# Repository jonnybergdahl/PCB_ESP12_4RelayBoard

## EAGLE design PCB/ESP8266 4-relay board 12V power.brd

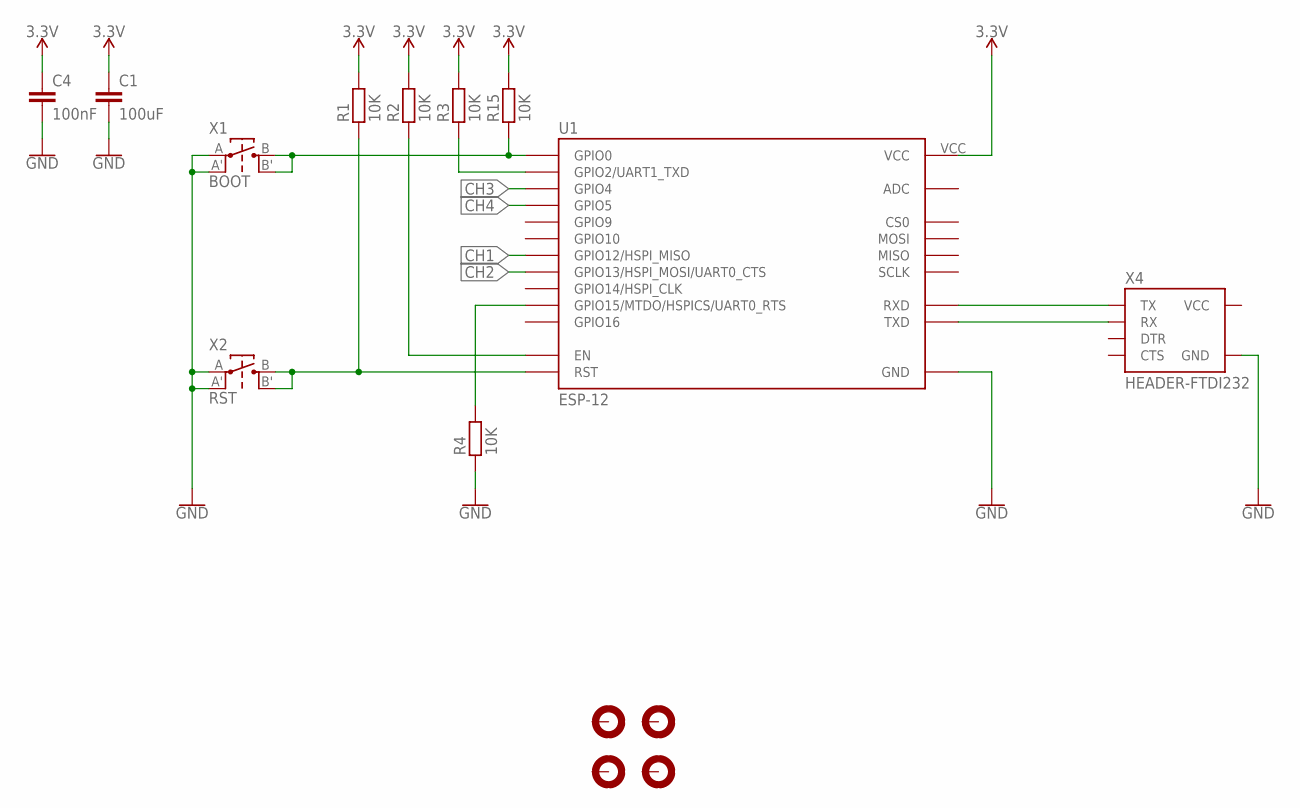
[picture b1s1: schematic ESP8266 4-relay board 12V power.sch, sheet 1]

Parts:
C1: 100uF; C0603
C4: 100nF; C0603
H1, H2, H3, H4: MOUNTHOLE-PAD3.2; 3.2-PAD
R1, R2, R3, R4, R15: 10K; R0603
U1: ESP-12; ESP-12E
X1: BOOT; TACT-SWITCH-EVQ
X2: RST; TACT-SWITCH-EVQ
X4: HEADER-FTDI232; FTDI232-1X06

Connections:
3.3V: C1.1, C4.1, R1.2, R2.2, R3.2, R15.2, U1.VCC; also elsewhere on the board
CH1: U1.GPIO12 (GPIO12/HSPI_MISO); also elsewhere on the board
CH2: U1.GPIO13 (GPIO13/HSPI_MOSI/UART0_CTS); also elsewhere on the board
CH3: U1.GPIO4; also elsewhere on the board
CH4: U1.GPIO5; also elsewhere on the board
GND: C1.2, C4.2, R4.1, U1.GND, X1.A, X1.A', X2.A, X2.A', X4.GND; also elsewhere on the board
unnamed: R4.2, U1.GPIO15 (GPIO15/MTDO/HSPICS/UART0_RTS)
unnamed: R2.1, U1.EN
unnamed: R1.1, U1.RST, X2.B, X2.B'
unnamed: R15.1, U1.GPIO0, X1.B, X1.B'
unnamed: R3.1, U1.GPIO2 (GPIO2/UART1_TXD)
RXD: U1.RXD, X4.TX
TXD: U1.TXD, X4.RX
VCC: X4.VCC

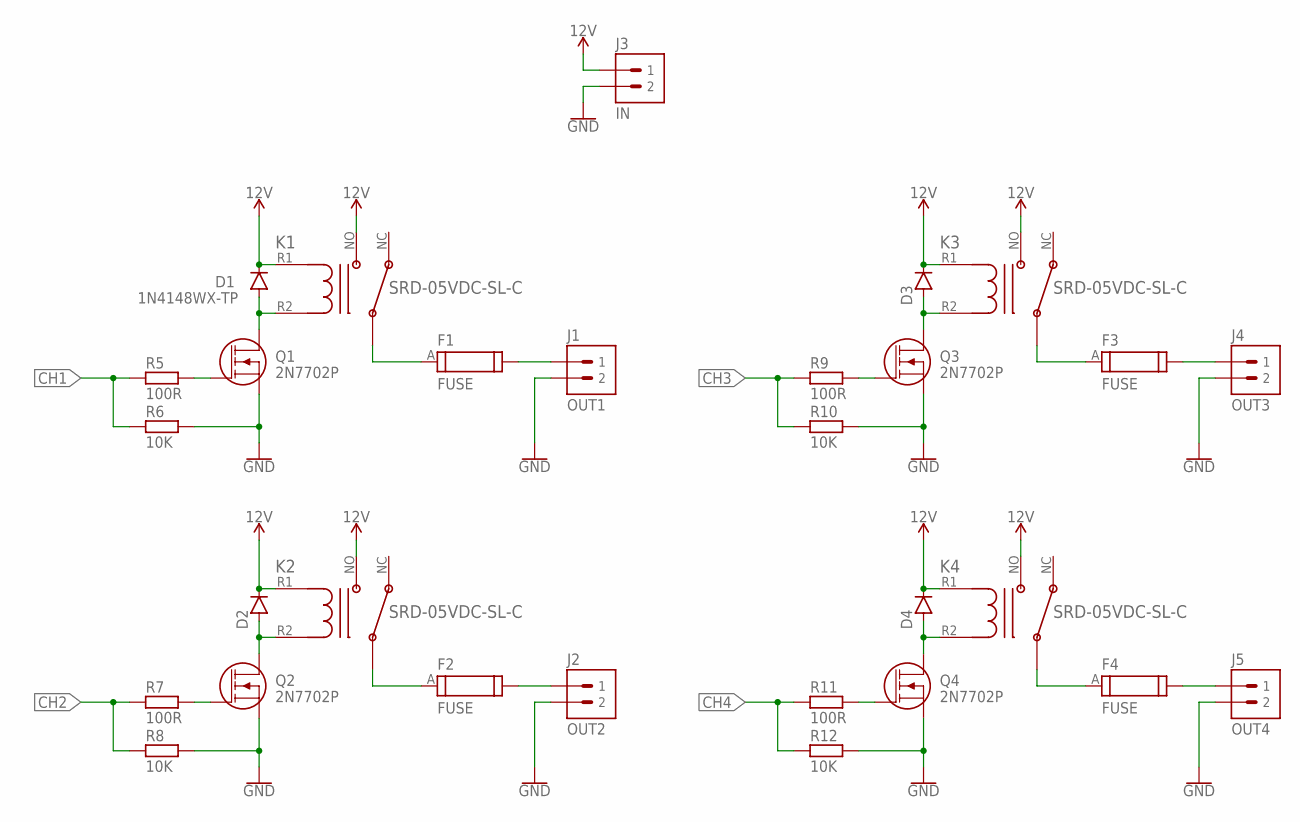
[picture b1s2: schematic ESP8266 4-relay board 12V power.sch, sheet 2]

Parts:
D1: 1N4148WX-TP; SOD-323
D2, D3, D4: DIODE1N4148WX-TP; SOD-323
F1, F2, F3, F4: FUSE; FUSE-TEAL
J1: OUT1; ONSHORE-OSTTC022162
J2: OUT2; ONSHORE-OSTTC022162
J3: IN; ONSHORE-OSTTC022162
J4: OUT3; ONSHORE-OSTTC022162
J5: OUT4; ONSHORE-OSTTC022162
K1, K2, K3, K4: SRD-05VDC-SL-C; RELAY-SRD-05VDC-SL-C
Q1, Q2, Q3, Q4: 2N7702P; SOT23-3
R5, R7, R9, R11: 100R; R0603
R6, R8, R10, R12: 10K; R0603

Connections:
12V: D1.1 (C), D2.1 (C), D3.1 (C), D4.1 (C), J3.1, K1.NO, K1.R1, K2.NO, K2.R1, K3.NO, K3.R1, K4.NO, K4.R1; also elsewhere on the board
CH1: R5.1, R6.1; also elsewhere on the board
CH2: R7.1, R8.1; also elsewhere on the board
CH3: R9.1, R10.1; also elsewhere on the board
CH4: R11.1, R12.1; also elsewhere on the board
GND: J1.2, J2.2, J3.2, J4.2, J5.2, Q1.2 (S), Q2.2 (S), Q3.2 (S), Q4.2 (S), R6.2, R8.2, R10.2, R12.2; also elsewhere on the board
unnamed: D1.2 (A), K1.R2, Q1.3 (D)
unnamed: F1.A, K1.C
unnamed: F1.B, J1.1
unnamed: Q1.1 (G), R5.2
unnamed: D2.2 (A), K2.R2, Q2.3 (D)
unnamed: Q2.1 (G), R7.2
unnamed: F2.A, K2.C
unnamed: F2.B, J2.1
unnamed: D3.2 (A), K3.R2, Q3.3 (D)
unnamed: F3.A, K3.C
unnamed: F3.B, J4.1
unnamed: Q3.1 (G), R9.2
unnamed: D4.2 (A), K4.R2, Q4.3 (D)
unnamed: Q4.1 (G), R11.2
unnamed: F4.A, K4.C
unnamed: F4.B, J5.1

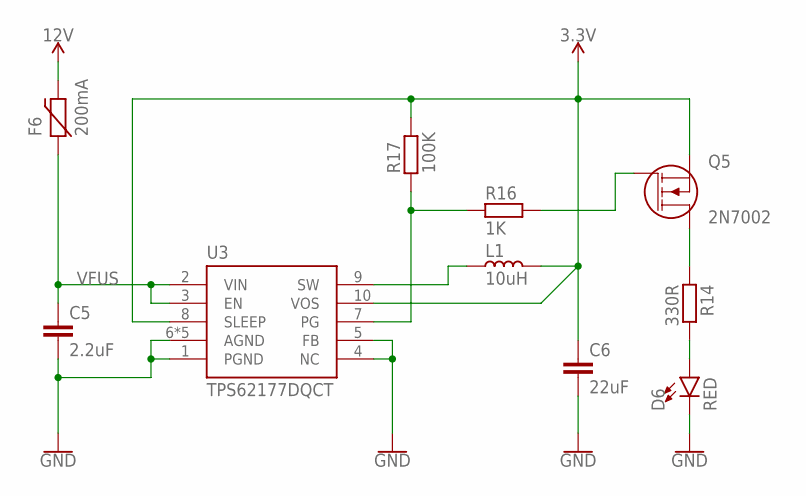
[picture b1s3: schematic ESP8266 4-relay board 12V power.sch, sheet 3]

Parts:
C5: 2.2uF; C0603
C6: 22uF; C0603
D6: RED; LED0603
F6: 200mA; PTC-0ZCJ-1206
L1: 10uH; TDK-VLS3015E
Q5: 2N7002; SOT23-3
R14: 330R; R0603
R16: 1K; R0603
R17: 100K; R0603
U3: TPS62177DQCT; WSON-10

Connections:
3.3V: C6.1, L1.2, Q5.2 (S), R17.2, U3.8 (SLEEP), U3.10 (VOS); also elsewhere on the board
12V: F6.2; also elsewhere on the board
GND: C5.2, C6.2, D6.C, U3.1 (PGND), U3.4 (NC), U3.5 (FB), U3.6 (AGND), U3.11 (AGND), U3.P$1 (AGND), U3.P$2 (AGND), U3.P$3 (AGND); also elsewhere on the board
unnamed: D6.A, R14.2
unnamed: R16.1, R17.1, U3.7 (PG)
unnamed: Q5.1 (G), R16.2
unnamed: Q5.3 (D), R14.1
SW1: L1.1, U3.9 (SW)
VFUS: C5.1, F6.1, U3.2 (VIN), U3.3 (EN)

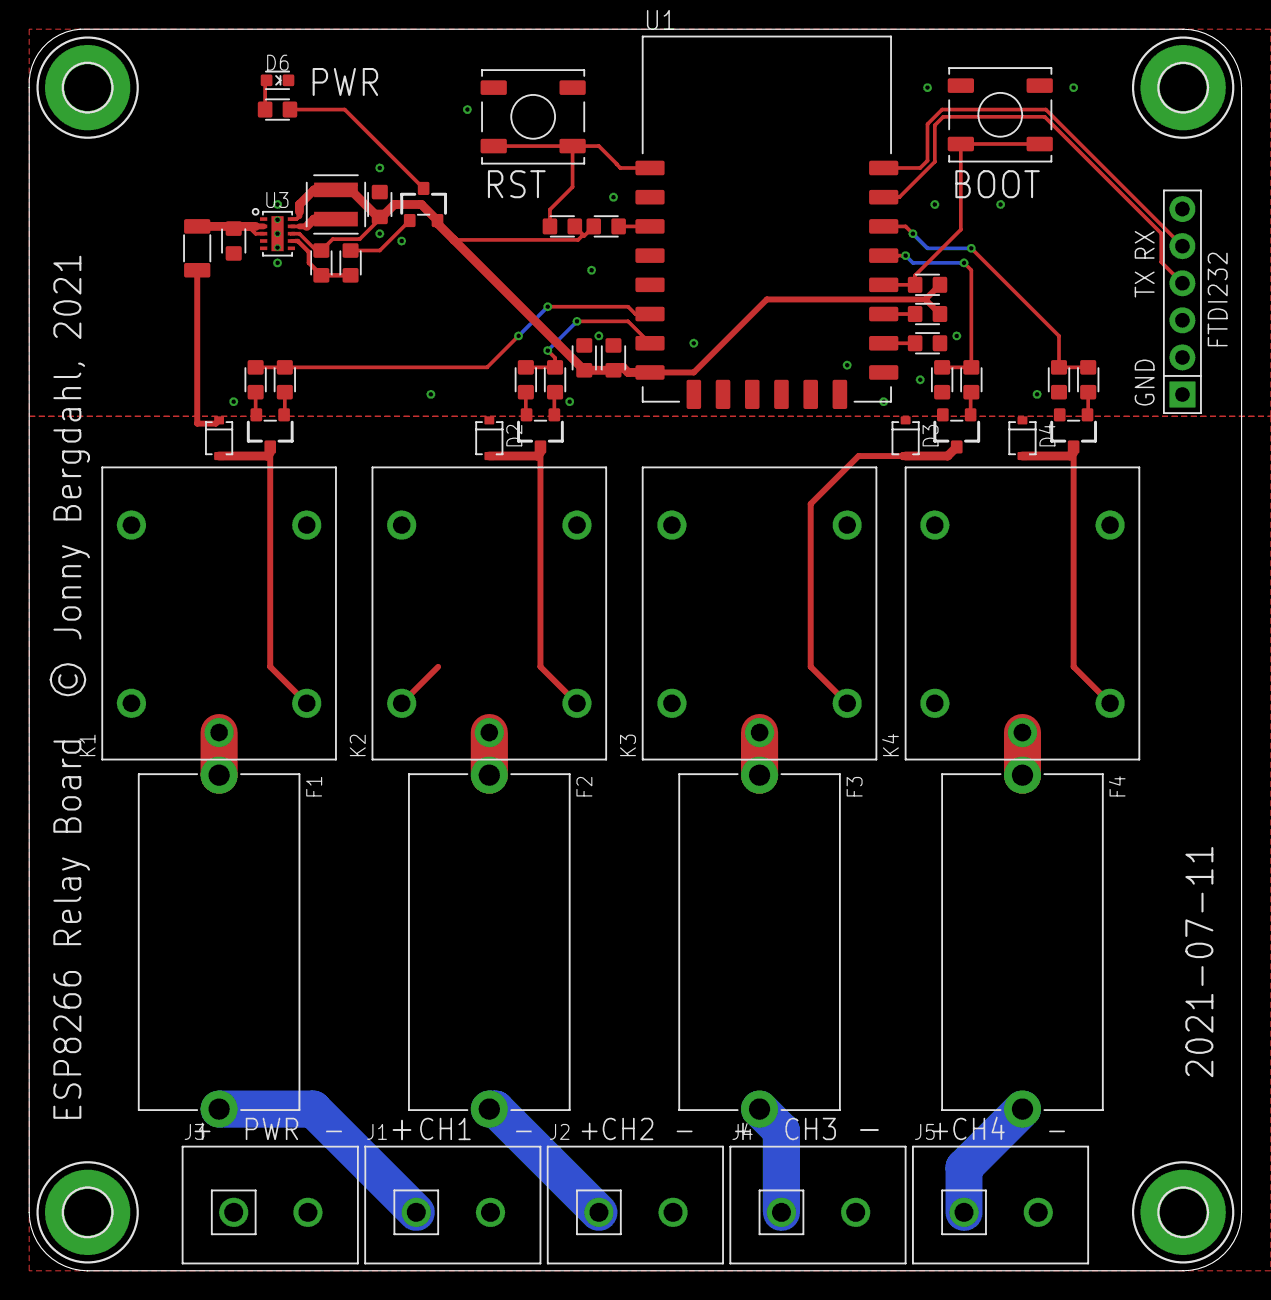
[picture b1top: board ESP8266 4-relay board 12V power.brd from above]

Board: 2 copper layers, 83.0 x 85.0 mm, 54 parts (0 on the bottom side), 36 nets.

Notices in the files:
PCB/ESP8266 4-relay board 12V power.brd:
© Jonny Bergdahl, 2021
